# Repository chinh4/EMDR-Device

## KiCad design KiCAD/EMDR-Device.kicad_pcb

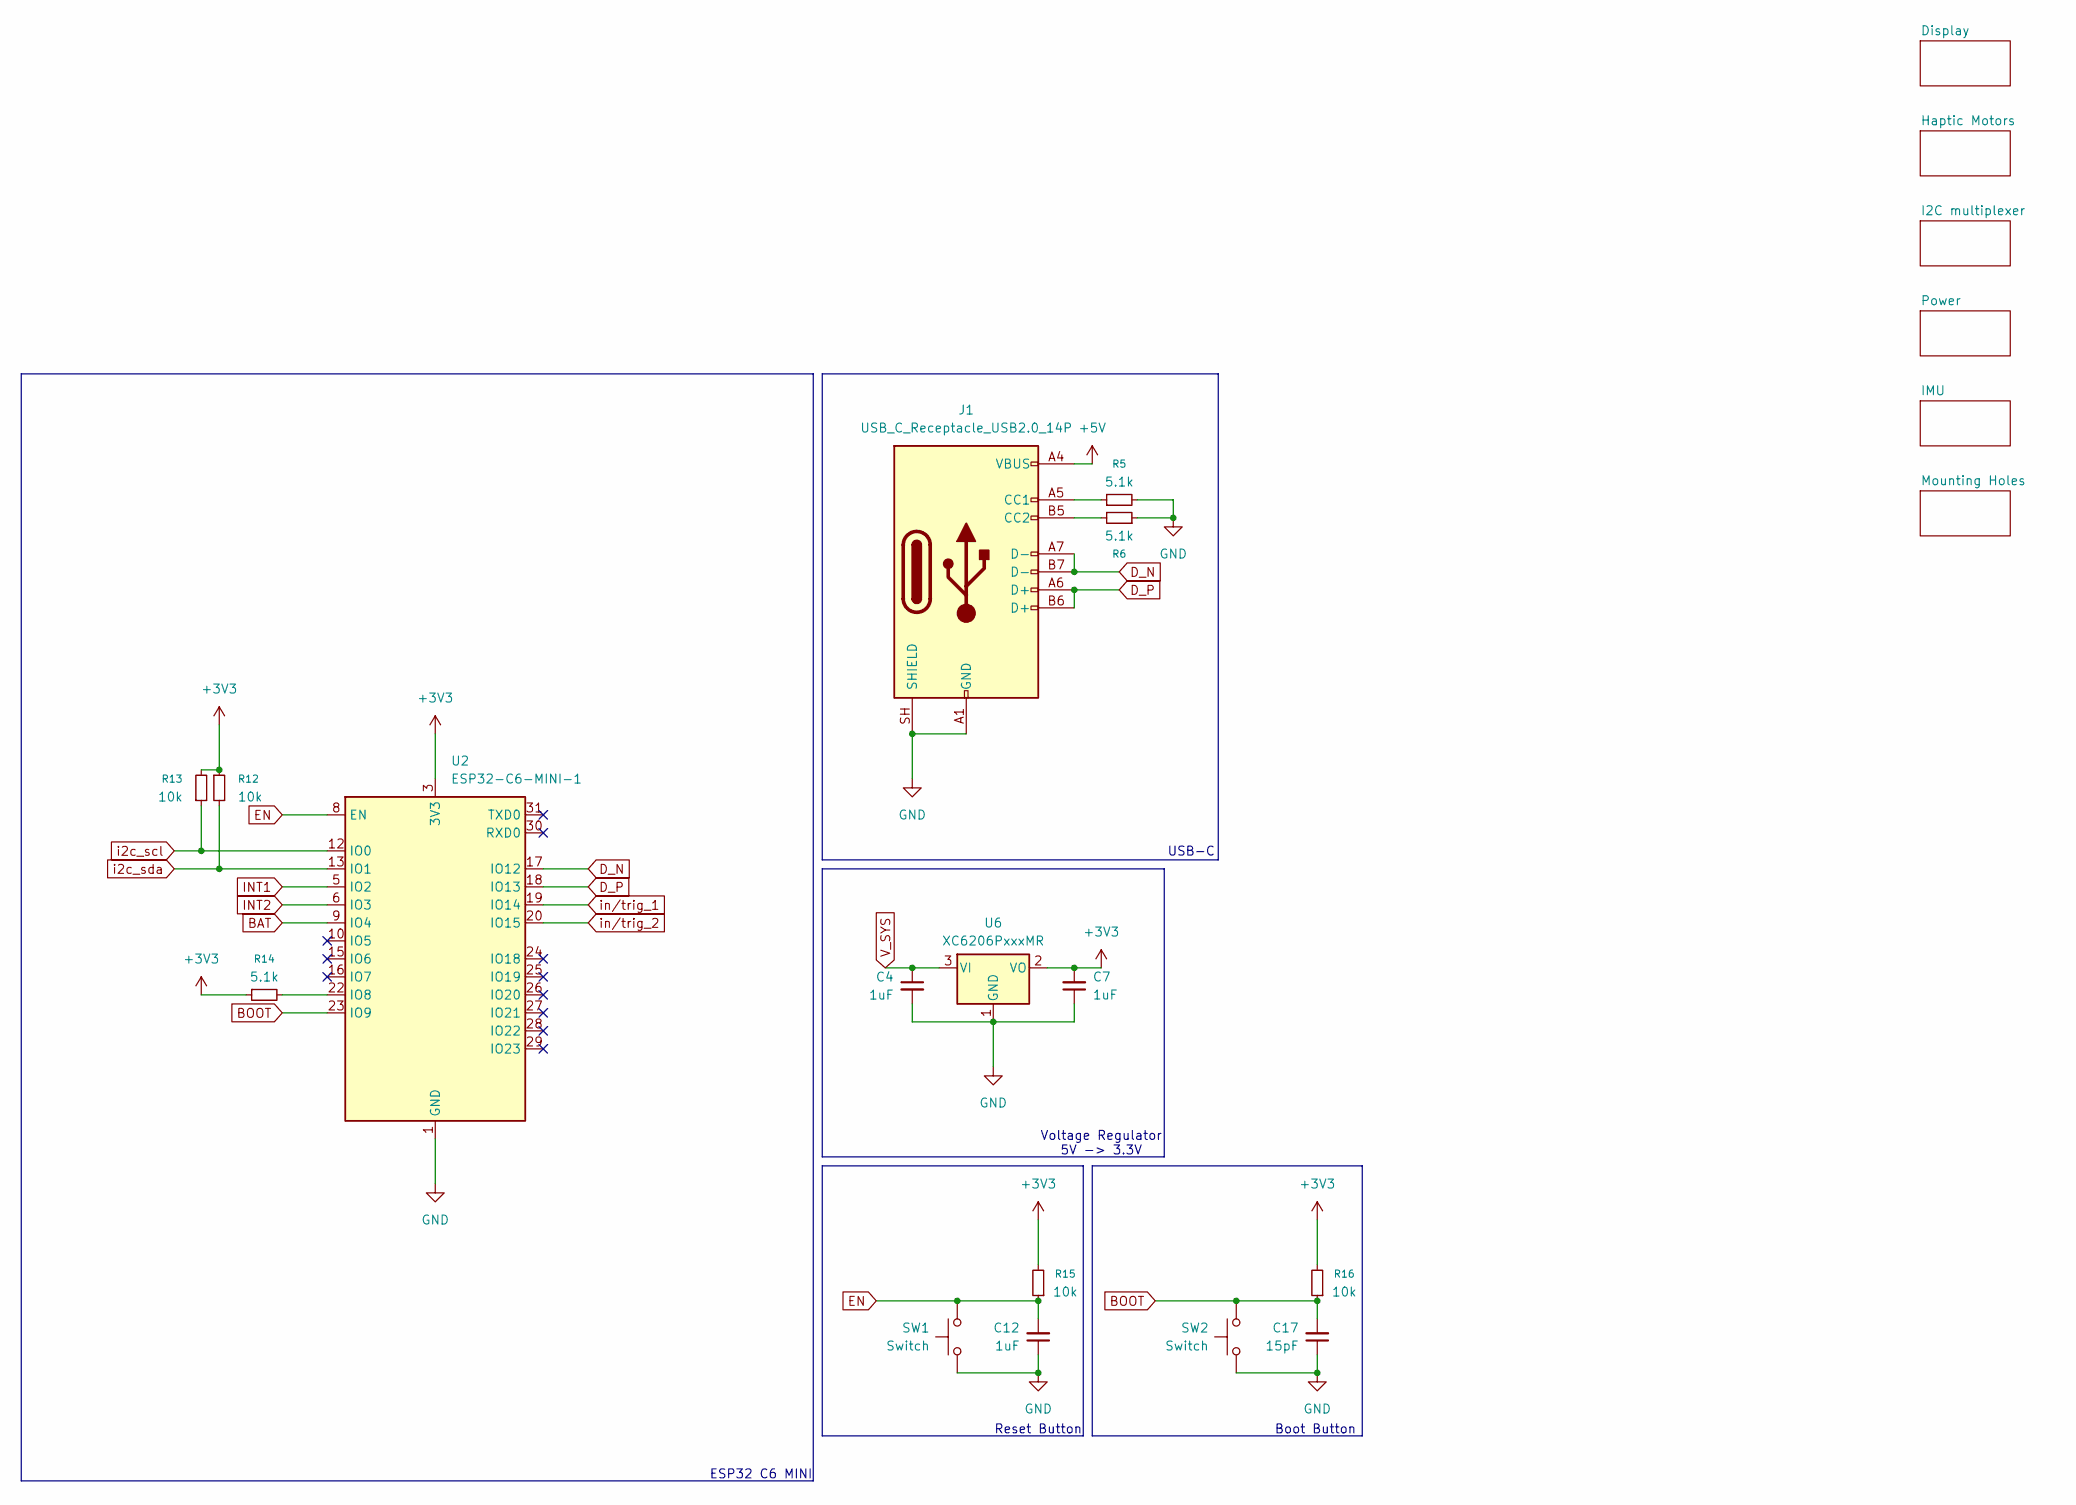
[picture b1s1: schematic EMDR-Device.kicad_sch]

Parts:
C4, C7, C12: 1uF; C_0603_1608Metric
C17: 15pF; C_0603_1608Metric
J1: USB_C_Receptacle_USB2.0_14P; USB_C_Receptacle_HCTL_HC-TYPE-C-16P-01A
R5, R6, R14: 5.1k; R_0603_1608Metric
R12, R13, R15, R16: 10k; R_0603_1608Metric
SW1, SW2: Switch; Panasonic_EVQPUJ_EVQPUA
U2: ESP32-C6-MINI-1
U6: XC6206PxxxMR; SOT-23-3

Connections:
+3V3: C7.2, R12.1, R13.2, R14.1, R15.2, R16.2, U2.3 (3V3), U6.2 (VO); also elsewhere on the board
+5V: J1.A4 (VBUS), J1.A9 (VBUS), J1.B4 (VBUS), J1.B9 (VBUS); also elsewhere on the board
BAT: U2.9 (IO4); also elsewhere on the board
BOOT: C17.2, R16.1, SW2.1, U2.23 (IO9)
D_N: J1.A7 (D-), J1.B7 (D-), U2.17 (IO12)
D_P: J1.A6 (D+), J1.B6 (D+), U2.18 (IO13)
EN: C12.2, R15.1, SW1.1, U2.8 (EN)
GND: C4.2, C7.1, C12.1, C17.1, J1.A1 (GND), J1.A12 (GND), J1.B1 (GND), J1.B12 (GND), J1.SH (SHIELD), R5.2, R6.1, SW1.2, SW2.2, U2.1 (GND), U2.2 (GND), U2.11 (GND), U2.14 (GND), U2.36 (GND), U2.37 (GND), U2.38 (GND), U2.39 (GND), U2.40 (GND), U2.41 (GND), U2.42 (GND), U2.43 (GND), U2.44 (GND), U2.45 (GND), U2.46 (GND), U2.47 (GND), U2.48 (GND), U2.49 (GND), U2.50 (GND), U2.51 (GND), U2.52 (GND), U2.53 (GND), U6.1 (GND); also elsewhere on the board
INT1: U2.5 (IO2); also elsewhere on the board
INT2: U2.6 (IO3); also elsewhere on the board
unnamed: J1.A5 (CC1), R5.1
unnamed: J1.B5 (CC2), R6.2
unnamed: R14.2, U2.22 (IO8)
V_SYS: C4.1, U6.3 (VI); also elsewhere on the board
i2c_scl: R13.1, U2.12 (IO0); also elsewhere on the board
i2c_sda: R12.2, U2.13 (IO1); also elsewhere on the board
in/trig_1: U2.19 (IO14); also elsewhere on the board
in/trig_2: U2.20 (IO15); also elsewhere on the board

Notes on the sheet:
Boot Button
USB-C
Voltage Regulator 5V -> 3.3V
ESP32 C6 MINI
Reset Button

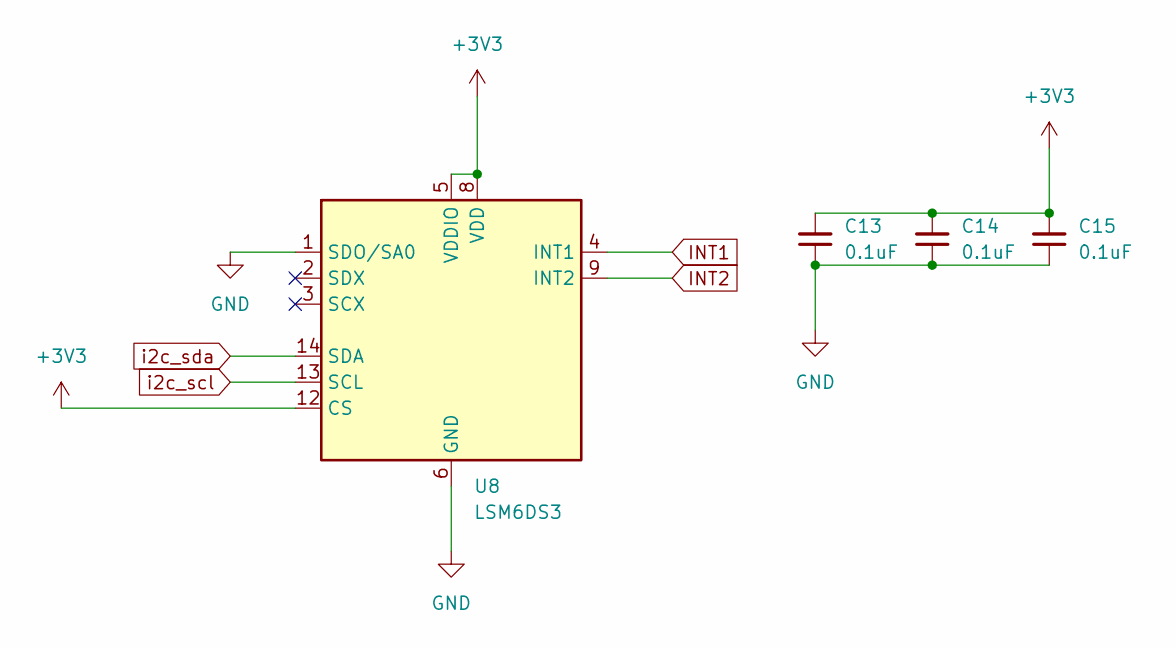
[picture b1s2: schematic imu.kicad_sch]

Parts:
C13, C14, C15: 0.1uF; C_0603_1608Metric
U8: LSM6DS3; LGA-14_3x2.5mm_P0.5mm_LayoutBorder3x4y

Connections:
+3V3: C13.2, C14.2, C15.2, U8.5 (VDDIO), U8.8 (VDD), U8.12 (CS); also elsewhere on the board
GND: C13.1, C14.1, C15.1, U8.1 (SDO/SA0), U8.6 (GND), U8.7 (GND); also elsewhere on the board
INT1: U8.4 (INT1); also elsewhere on the board
INT2: U8.9 (INT2); also elsewhere on the board
i2c_scl: U8.13 (SCL); also elsewhere on the board
i2c_sda: U8.14 (SDA); also elsewhere on the board

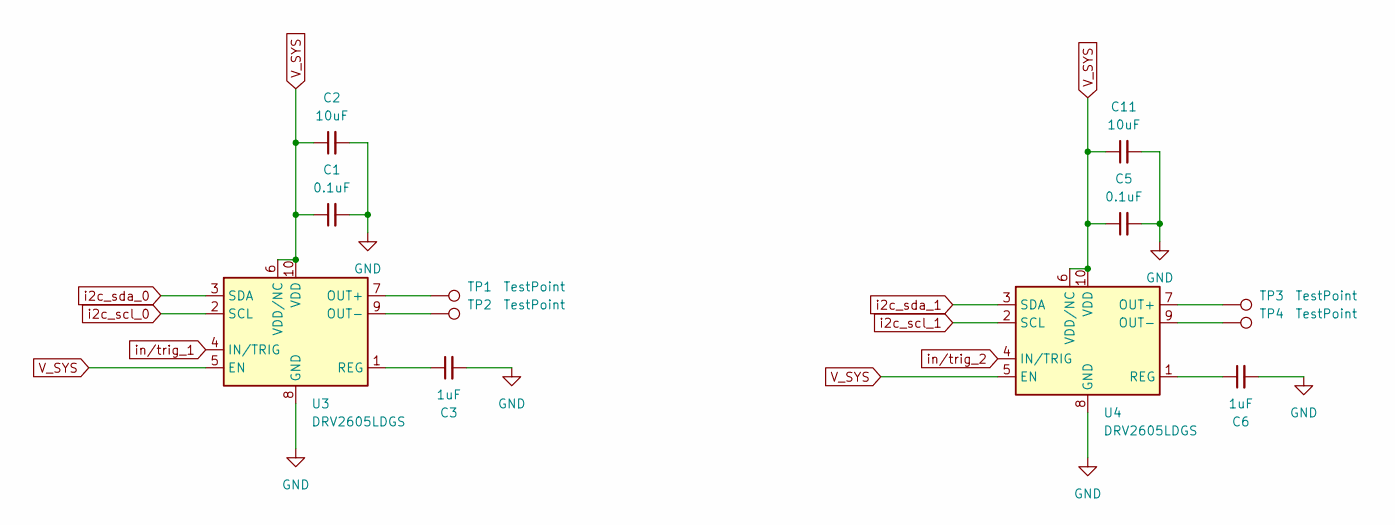
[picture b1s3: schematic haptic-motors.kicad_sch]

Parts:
C1, C5: 0.1uF; C_0603_1608Metric
C2, C11: 10uF; C_0603_1608Metric
C3, C6: 1uF; C_0603_1608Metric
TP1, TP2, TP3, TP4: TestPoint; Pin_D1.0mm_L10.0mm
U3, U4: DRV2605LDGS; TSSOP-10_3x3mm_P0.5mm

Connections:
GND: C1.2, C2.2, C3.2, C5.2, C6.2, C11.2, U3.8 (GND), U4.8 (GND); also elsewhere on the board
unnamed: TP1.1 (1_1), U3.7 (OUT+)
unnamed: TP2.1 (1_1), U3.9 (OUT-)
unnamed: C3.1, U3.1 (REG)
unnamed: TP3.1 (1_1), U4.7 (OUT+)
unnamed: TP4.1 (1_1), U4.9 (OUT-)
unnamed: C6.1, U4.1 (REG)
V_SYS: C1.1, C2.1, C5.1, C11.1, U3.5 (EN), U3.6 (VDD/NC), U3.10 (VDD), U4.5 (EN), U4.6 (VDD/NC), U4.10 (VDD); also elsewhere on the board
i2c_scl_0: U3.2 (SCL); also elsewhere on the board
i2c_scl_1: U4.2 (SCL); also elsewhere on the board
i2c_sda_0: U3.3 (SDA); also elsewhere on the board
i2c_sda_1: U4.3 (SDA); also elsewhere on the board
in/trig_1: U3.4 (IN/TRIG); also elsewhere on the board
in/trig_2: U4.4 (IN/TRIG); also elsewhere on the board

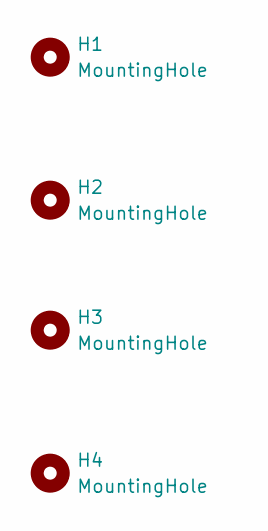
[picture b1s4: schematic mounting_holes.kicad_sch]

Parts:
H1, H2, H3, H4: MountingHole; MountingHole_3.2mm_M3_DIN965_Pad

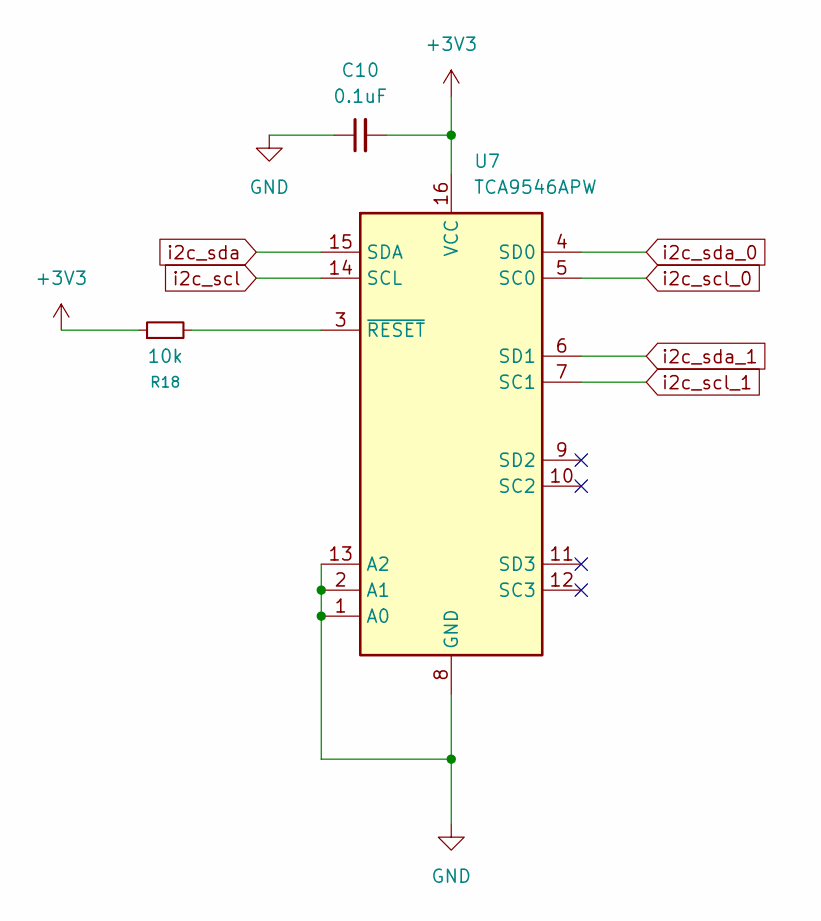
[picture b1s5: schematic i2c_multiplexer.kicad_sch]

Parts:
C10: 0.1uF; C_0603_1608Metric
R18: 10k; R_0603_1608Metric
U7: TCA9546APW; TSSOP-16_4.4x5mm_P0.65mm

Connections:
+3V3: C10.2, R18.1, U7.16 (VCC); also elsewhere on the board
GND: C10.1, U7.1 (A0), U7.2 (A1), U7.8 (GND), U7.13 (A2); also elsewhere on the board
unnamed: R18.2, U7.3 (~RESET)
i2c_scl: U7.14 (SCL); also elsewhere on the board
i2c_scl_0: U7.5 (SC0); also elsewhere on the board
i2c_scl_1: U7.7 (SC1); also elsewhere on the board
i2c_sda: U7.15 (SDA); also elsewhere on the board
i2c_sda_0: U7.4 (SD0); also elsewhere on the board
i2c_sda_1: U7.6 (SD1); also elsewhere on the board

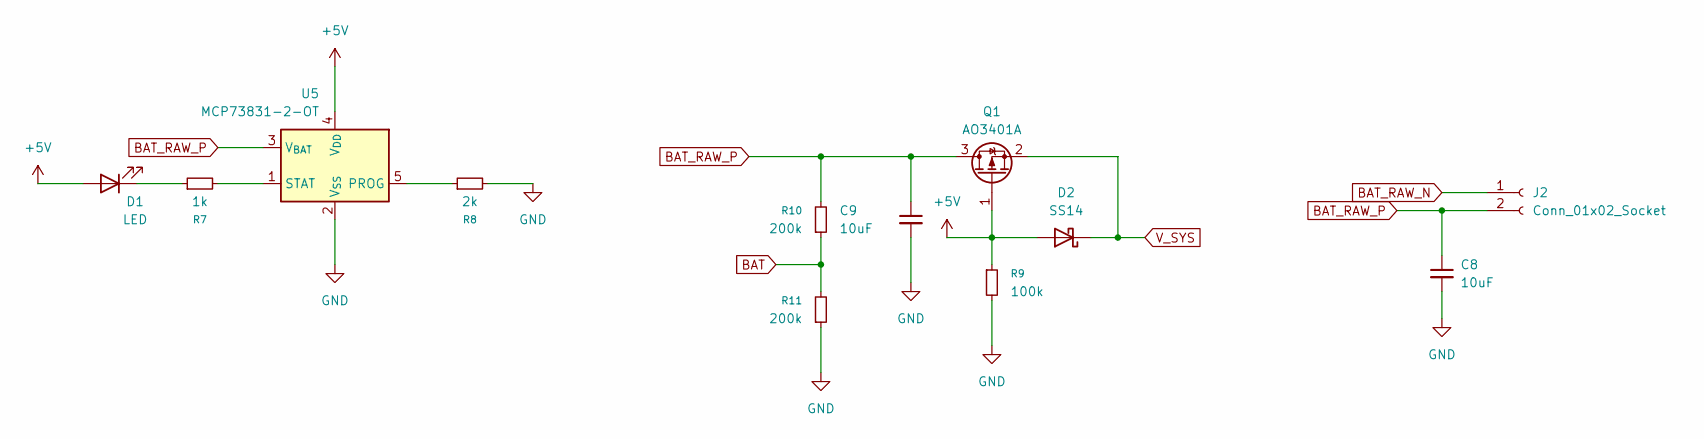
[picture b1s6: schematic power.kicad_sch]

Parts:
C8, C9: 10uF; C_0603_1608Metric
D1: LED; LED_0603_1608Metric
D2: SS14; D_SMA
J2: Conn_01x02_Socket; JST_PH_S2B-PH-K_1x02_P2.00mm_Horizontal
Q1: AO3401A; SOT-23
R7: 1k; R_0603_1608Metric
R8: 2k; R_0603_1608Metric
R9: 100k; R_0603_1608Metric
R10, R11: 200k; R_0603_1608Metric
U5: MCP73831-2-OT; SOT-23-5

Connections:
+5V: D1.2 (A), D2.2 (A), Q1.1 (G), R9.1, U5.4 (V_{DD}); also elsewhere on the board
BAT: R10.1, R11.2; also elsewhere on the board
BAT_RAW_N: J2.1
BAT_RAW_P: C8.1, C9.1, J2.2, Q1.3 (D), R10.2, U5.3 (V_{BAT})
GND: C8.2, C9.2, R8.2, R9.2, R11.1, U5.2 (V_{SS}); also elsewhere on the board
unnamed: D1.1 (K), R7.1
unnamed: R8.1, U5.5 (PROG)
unnamed: R7.2, U5.1 (STAT)
V_SYS: D2.1 (K), Q1.2 (S); also elsewhere on the board

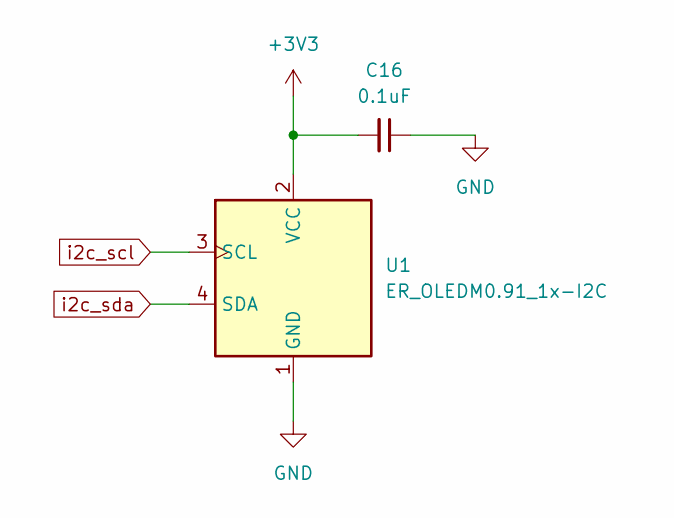
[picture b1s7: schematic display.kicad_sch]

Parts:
C16: 0.1uF; C_0603_1608Metric
U1: ER_OLEDM0.91_1x-I2C

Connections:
+3V3: C16.2, U1.2 (VCC); also elsewhere on the board
GND: C16.1, U1.1 (GND); also elsewhere on the board
i2c_scl: U1.3 (SCL); also elsewhere on the board
i2c_sda: U1.4 (SDA); also elsewhere on the board

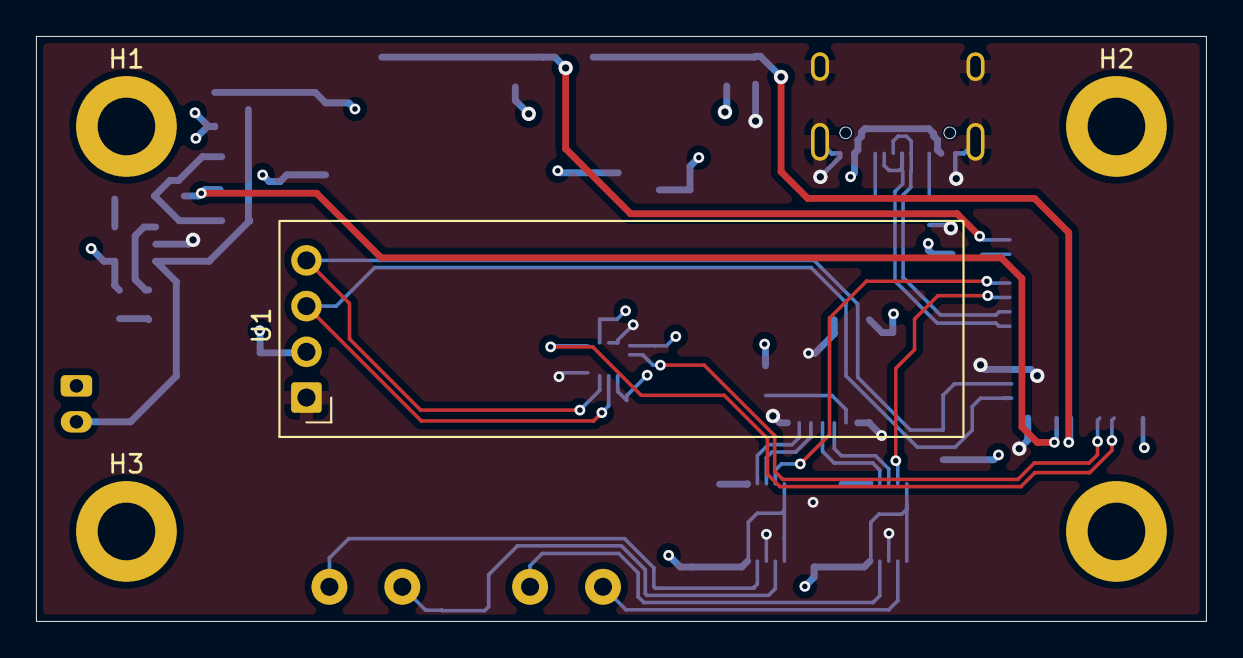
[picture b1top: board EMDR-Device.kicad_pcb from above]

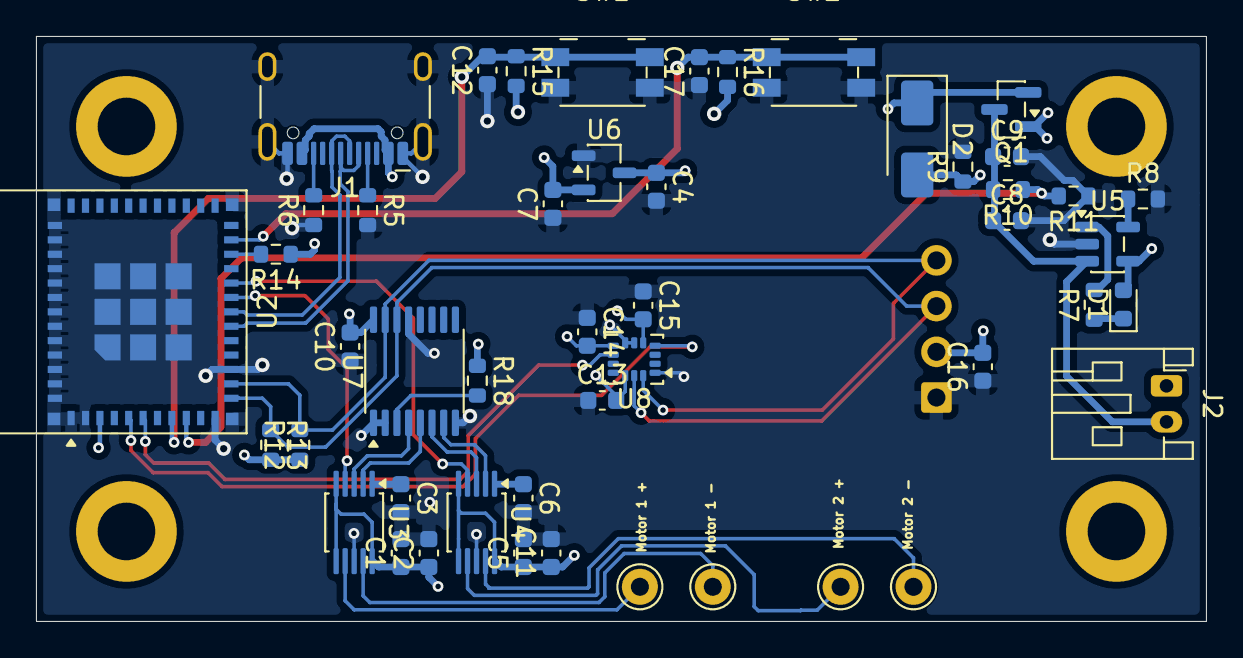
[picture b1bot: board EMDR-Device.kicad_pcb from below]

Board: 4 copper layers, 65.0 x 32.5 mm, 53 parts (48 on the bottom side), 33 nets.
